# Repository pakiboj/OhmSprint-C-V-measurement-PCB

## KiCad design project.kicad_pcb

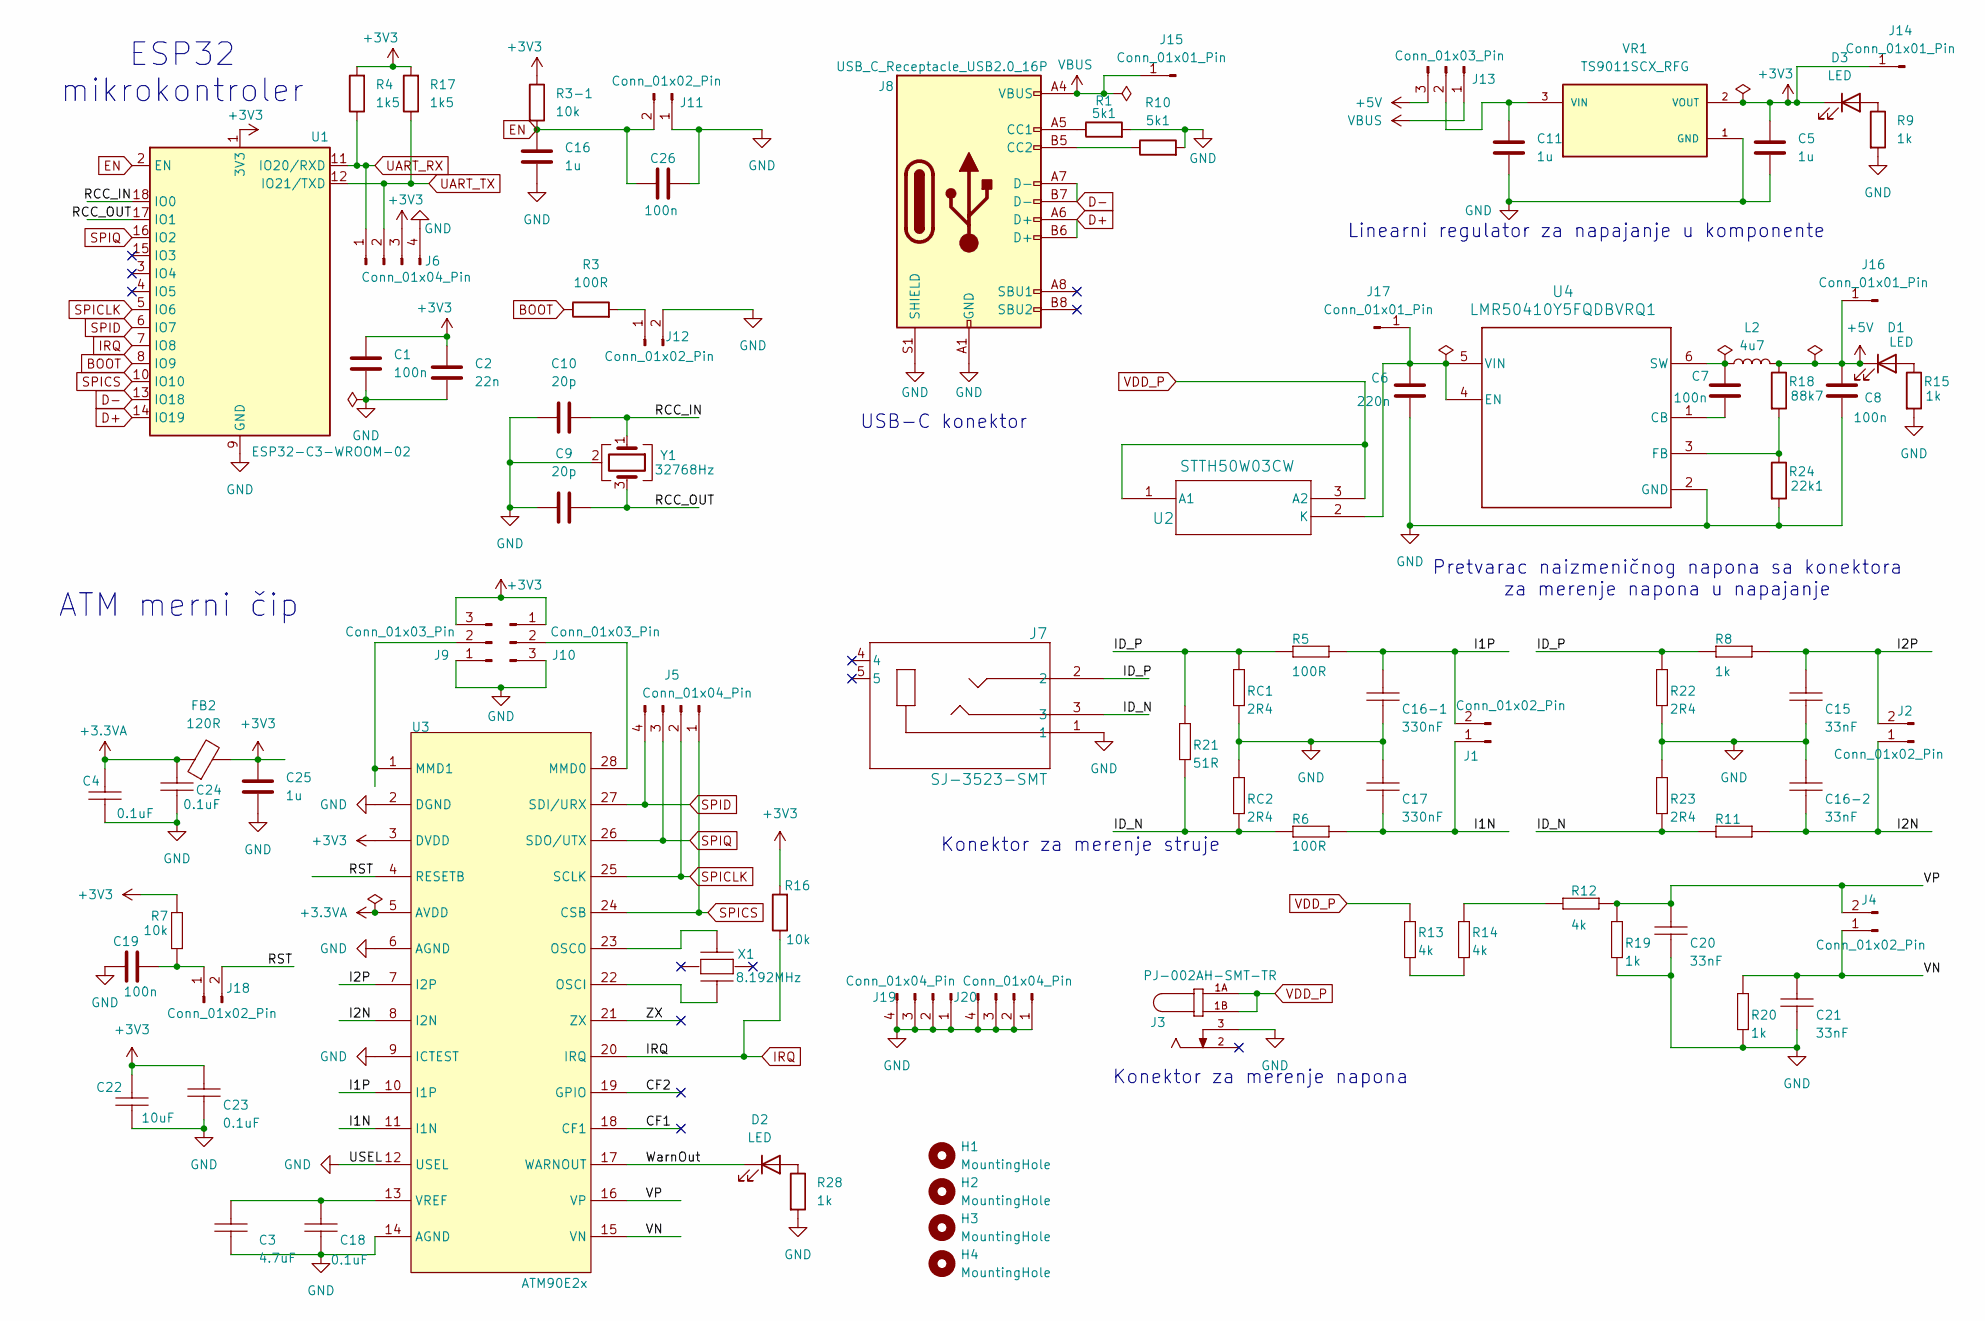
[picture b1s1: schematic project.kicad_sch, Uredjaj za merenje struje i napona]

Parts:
C1, C7, C8, C19, C26: 100n; C_0603_1608Metric; MPN 0603B104K250SD
C2: 22n; C_0603_1608Metric; MPN 0603B223K500SD
C3: 4.7uF; C_0805_2012Metric; MPN 0805B475K250CC
C4, C18: 0.1uF; C_0805_2012Metric; MPN 0805B104J500BD
C5, C11, C16, C25: 1u; C_0805_2012Metric; MPN 0805B105K250CC
C6: 220n; C_0805_2012Metric; MPN 0805B224K500CC
C9, C10: 20p; C_0603_1608Metric; MPN 0603N200J500SD
C15, C16-2, C20, C21: 33nF; C_0805_2012Metric; MPN 0805B333K500BD
C16-1, C17: 330nF; C_0603_1608Metric; MPN 0805B334K500CC
C22: 10uF; C_0805_2012Metric; MPN 0805B334K500CC
C23, C24: 0.1uF; C_0603_1608Metric; MPN 0603B104K250SD
D1, D2, D3: LED; D_1206_3216Metric; MPN XL-3216SURC
FB2: 120R; L_0805_2012Metric; MPN LI0805H121R-10
H1, H2, H3, H4: MountingHole; MountingHole_2mm
J1, J2, J4, J11, J12, J18: Conn_01x02_Pin; AMASS_XT30U-F_1x02_P5.0mm_Vertical; MPN PRPC002SAAN-RC
J3: PJ-002AH-SMT-TR; CUI_PJ-002AH-SMT-TR; MPN PJ-002AH-SMT-TR
J5, J6, J19, J20: Conn_01x04_Pin; FanPinHeader_1x04_P2.54mm_Vertical; MPN 68002-404HLF
J7: SJ-3523-SMT; SJ-3523-SMT_CUD; MPN SJ-3523-SMT-TR
J8: USB_C_Receptacle_USB2.0_16P; USB_C_Receptacle_GCT_USB4105-xx-A_16P_TopMnt_Horizontal; MPN UJ20-C-H-G-SMT-TR
J9, J10, J13: Conn_01x03_Pin; FanPinHeader_1x03_P2.54mm_Vertical; MPN 68001-203HLF
J14, J15, J16, J17: Conn_01x01_Pin; Hirose_DF63M-1P-3.96DSA_1x01_P3.96mm_Vertical; MPN 68000-101HLF
L2: 4u7; L_0805_2012Metric; MPN 0805LS-222XJRC
R1, R10: 5k1; R_0805_2012Metric; MPN CR0805-JW-512ELF
R3, R5, R6: 100R; R_0805_2012Metric; MPN CR0805-FX-1000ELF
R3-1, R7, R16: 10k; R_0805_2012Metric; MPN CR0805-FX-1002ELF
R4, R17: 1k5; R_0805_2012Metric; MPN CR0805-JW-152ELF
R8, R9, R11, R15, R19, R20, R28: 1k; R_0805_2012Metric; MPN CR0805-FX-1001ELF
R12, R13, R14: 4k; R_0805_2012Metric; MPN CR0805-FX-4021ELF
R18: 88k7; R_0805_2012Metric; MPN CR0805-FX-1001ELF
R21: 51R; R_0805_2012Metric; MPN CR0805-FX-51R0ELF
R22, R23: 2R4; R_0805_2012Metric; MPN CR0805-FX-2401ELF
R24: 22k1; R_0805_2012Metric; MPN CR0805-FX-1001ELF
RC1, RC2: 2R4; R_0805_2012Metric; MPN CR0805-FX-2401ELF
U1: ESP32-C3-WROOM-02; MPN ESP32-C3-WROOM-02-N4
U2: STTH50W03CW; TO-247_15P75X5P1_STM; MPN STTH50W03CW
U3: ATM90E2x; SSOP28_10P3X5P4_MCH; MPN ATM90E26-YU-R
U4: LMR50410Y5FQDBVRQ1; DBV0006A-IPC_C; MPN LMR50410Y5FQDBVRQ1
VR1: TS9011SCX_RFG; VREG_TS9011SCX_RFG; PARTREV I2402
X1: 8.192MHz; OSC_ECS-2520S25-250-FN-TR; MPN XTAL OSC XO 8.192MHZ CMOS SMD
Y1: 32768Hz; OSC_ECS-2520S25-250-FN-TR; MPN XTAL OSC XO 32.7680KHZ SMD

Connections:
+3.3VA: C4.2, C24.2, FB2.1, U3.5 (AVDD)
+3V3: C1.1, C2.1, C5.1, C22.1, C23.2, C25.1, D3.1 (K), FB2.2, J6.3, J9.3, J10.1, J14.1, R3-1.1, R4.2, R7.2, R16.2, R17.2, U1.1 (3V3), U3.3 (DVDD), VR1.2 (VOUT)
+5V: C8.1, D1.1 (K), J13.3, J16.1, L2.2, R18.1
/CF1: U3.18 (CF1)
/CF2: U3.19 (GPIO)
/I1N: C17.1, J1.1, R6.1, U3.11 (I1N)
/I1P: C16-1.2, J1.2, R5.1, U3.10 (I1P)
/I2N: C16-2.1, J2.1, R11.1, U3.8 (I2N)
/I2P: C15.2, J2.2, R8.1, U3.7 (I2P)
/ID_N: J7.3, R6.2, R11.2, R21.1, R23.1, RC2.1
/ID_P: J7.2, R5.2, R8.2, R21.2, R22.2, RC1.2
/RCC_IN: C10.2, U1.18 (IO0), Y1.1
/RCC_OUT: C9.2, U1.17 (IO1), Y1.3
/RST: J18.2, U3.4 (RESETB)
/VN: C21.2, J4.1, R20.2, U3.15 (VN)
/VP: C20.2, J4.2, R12.2, R19.2, U3.16 (VP)
/WarnOut: D2.1 (K), U3.17 (WARNOUT)
/ZX: U3.21 (ZX)
BOOT: R3.1, U1.8 (IO9)
D+: J8.A6 (D+), J8.B6 (D+), U1.14 (IO19)
D-: J8.A7 (D-), J8.B7 (D-), U1.13 (IO18)
EN: C16.1, C26.1, J11.2, R3-1.2, U1.2 (EN)
GND: C1.2, C2.2, C3.1, C4.1, C5.2, C6.2, C8.2, C9.1, C10.1, C11.2, C15.1, C16.2, C16-1.1, C16-2.2, C17.2, C18.1, C19.1, C20.1, C21.1, C22.2, C23.1, C24.1, C25.2, C26.2, J3.3, J6.4, J7.1, J8.A1 (GND), J8.A12 (GND), J8.B1 (GND), J8.B12 (GND), J8.S1 (SHIELD), J9.1, J10.3, J11.1, J12.2, J19.1, J19.2, J19.3, J19.4, J20.1, J20.2, J20.3, J20.4, R1.2, R9.2, R10.2, R15.2, R19.1, R20.1, R22.1, R23.2, R24.2, R28.2, RC1.1, RC2.2, U1.9 (GND), U1.19 (GND), U3.2 (DGND), U3.6 (AGND), U3.9 (ICTEST), U3.12 (USEL), U3.14 (AGND), U4.2 (GND), VR1.1 (GND), Y1.2 (G), Y1.4 (G)
IRQ: R16.1, U1.7 (IO8), U3.20 (IRQ)
unnamed: D1.2 (A), R15.1
unnamed: D2.2 (A), R28.1
unnamed: D3.2 (A), R9.1
unnamed: J8.A5 (CC1), R1.1
unnamed: J8.B5 (CC2), R10.1
unnamed: J9.2, U3.1 (MMD1)
unnamed: J10.2, U3.28 (MMD0)
unnamed: J12.1, R3.2
unnamed: C11.1, J13.2, VR1.3 (VIN)
unnamed: C6.1, J17.1, U2.2 (K), U4.4 (EN), U4.5 (VIN)
unnamed: C19.2, J18.1, R7.1
unnamed: R12.1, R14.1
unnamed: R13.2, R14.2
unnamed: U3.22 (OSCI), X1.2
unnamed: U3.23 (OSCO), X1.1
unnamed: C3.2, C18.2, U3.13 (VREF)
unnamed: C7.2, U4.1 (CB)
unnamed: R18.2, R24.1, U4.3 (FB)
unnamed: C7.1, L2.1, U4.6 (SW)
SPICLK: J5.2, U1.5 (IO6), U3.25 (SCLK)
SPICS: J5.1, U1.10 (IO10), U3.24 (CSB)
SPID: J5.4, U1.6 (IO7), U3.27 (SDI/URX)
SPIQ: J5.3, U1.16 (IO2), U3.26 (SDO/UTX)
UART_RX: J6.1, R4.1, U1.11 (IO20/RXD)
UART_TX: J6.2, R17.1, U1.12 (IO21/TXD)
VBUS: J8.A4 (VBUS), J8.A9 (VBUS), J8.B4 (VBUS), J8.B9 (VBUS), J13.1, J15.1
VDD_P: J3.1A, J3.1B, R13.1, U2.1 (A1), U2.3 (A2)

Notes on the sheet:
ATM merni čip
USB-C konektor
Konektor za merenje struje
ESP32 mikrokontroler
Konektor za merenje napona
Linearni regulator za napajanje u komponente
Pretvarac naizmeničnog napona sa konektora za merenje napona u napajanje

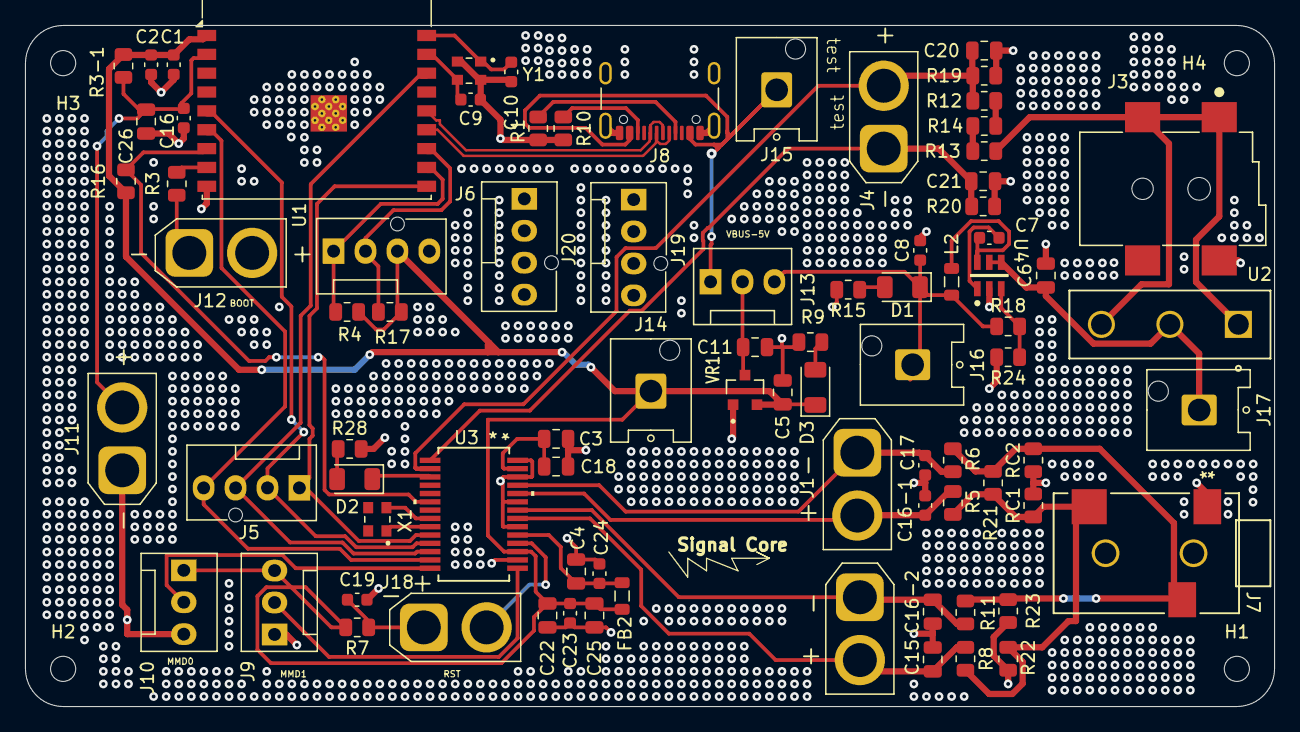
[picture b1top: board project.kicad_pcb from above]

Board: 2 copper layers, 99.4 x 54.2 mm, 88 parts (0 on the bottom side), 48 nets.

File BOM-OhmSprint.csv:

"Reference","Qty","Exclude from BOM","Exclude from Board","Datasheet","Footprint","Value","MANUFACTURER","MPN","link"
"C1,C7,C8,C19,C26","5","","","~","Capacitor_SMD:C_0603_1608Metric","100n","NextGen Components","0603B104K250SD","https://www.digikey.com/en/products/detail/nextgen-component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"
"C2","1","","","~","Capacitor_SMD:C_0603_1608Metric","22n","NextGen Components","0603B223K500SD","https://www.digikey.com/en/products/detail/nextgen-component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"
"C3","1","","","","Capacitor_SMD:C_0805_2012Metric","4.7uF","NextGen Components","0805B475K250CC","https://www.digikey.com/en/products/detail/nextgen-component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"
"C4,C18","2","","","","Capacitor_SMD:C_0805_2012Metric","0.1uF","NextGen Components","0805B104J500BD","https://www.digikey.com/en/products/detail/nextgen-component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"
"C5,C11,C16,C25","4","","","~","Capacitor_SMD:C_0805_2012Metric","1u","Aillen","0805B105K250CC","https://www.digikey.com/en/products/detail/nextgen-component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"
"C6","1","","","~","Capacitor_SMD:C_0805_2012Metric","220n","NextGen Components","0805B224K500CC","https://www.digikey.com/en/products/detail/nextgen-component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"
"C9,C10","2","","","~","Capacitor_SMD:C_0603_1608Metric","20p","NextGen Components","0603N200J500SD","https://www.digikey.com/en/products/detail/nextgen-component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"
"C15,C16-2,C20,C21","4","","","","Capacitor_SMD:C_0805_2012Metric","33nF","NextGen Components","0805B333K500BD","https://www.digikey.com/en/products/detail/nextgen-component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"
"C16-1,C17","2","","","","Capacitor_SMD:C_0603_1608Metric","330nF","NextGen Components","0805B334K500CC","https://www.digikey.com/en/products/detail/nextgen-component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"
"C22","1","","","","Capacitor_SMD:C_0805_2012Metric","10uF","NextGen Components","0805B334K500CC","https://www.digikey.com/en/products/detail/nextgen-component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"
"C23,C24","2","","","","Capacitor_SMD:C_0603_1608Metric","0.1uF","NextGen Components","0603B104K250SD","https://www.digikey.com/en/products/detail/nextgen-component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"
"D1,D2,D3","3","","","~","Diode_SMD:D_1206_3216Metric","LED","XINGLIGHT","XL-3216SURC","https://www.digikey.com/en/products/detail/xinglight/XL-3216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"
"FB2","1","","","~","Inductor_SMD:L_0805_2012Metric","120R","Laird-Signal Integrity Products","LI0805H121R-10","https://www.digikey.com/en/products/detail/laird-signal-inte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"
"H1,H2,H3,H4","4","Excluded from BOM","","~","MountingHole:MountingHole_2mm","MountingHole","","",""
"J1,J2,J4,J11,J12,J18","6","","","~","Connector_AMASS:AMASS_XT30U-F_1x02_P5.0mm_Vertical","Conn_01x02_Pin","Sullins Connector Solutions","PRPC002SAAN-RC","https://www.digikey.com/en/products/detail/sullins-connector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"
"J3","1","","","","OhmSprint:CUI_PJ-002AH-SMT-TR","PJ-002AH-SMT-TR","Same Sky (Formerly CUI Devices)","PJ-002AH-SMT-TR","https://www.digikey.com/en/products/detail/same-sky-formerly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"
"J5,J6,J19,J20","4","","","~","Connector:FanPinHeader_1x04_P2.54mm_Vertical","Conn_01x04_Pin","Amphenol ICC (FCI)","68002-404HLF","https://www.digikey.com/en/products/detail/amphenol-cs-fci/6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"
"J7","1","","","SJ-3523-SMT","OhmSprint:SJ-3523-SMT_CUD","SJ-3523-SMT","Same Sky (Formerly CUI Devices)","SJ-3523-SMT-TR","https://www.digikey.com/en/products/detail/same-sky-formerly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"
"J8","1","","","USB_C_Receptacle_USB2.0_16P","Connector_USB:USB_C_Receptacle_GCT_USB4105-xx-A_16P_TopMnt_Horizontal","USB_C_Receptacle_USB2.0_16P","Same Sky (Formerly CUI Devices)","UJ20-C-H-G-SMT-TR","https://www.digikey.com/en/products/detail/same-sky-formerly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"
"J9,J10,J13","3","","","~","Connector:FanPinHeader_1x03_P2.54mm_Vertical","Conn_01x03_Pin","Amphenol ICC (FCI)","68001-203HLF","https://www.digikey.com/en/products/detail/amphenol-cs-fci/6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"
"J14,J15,J16,J17","4","","","~","Connector_Hirose:Hirose_DF63M-1P-3.96DSA_1x01_P3.96mm_Vertical","Conn_01x01_Pin","Amphenol ICC (FCI)","68000-101HLF","https://www.digikey.com/en/products/detail/amphenol-cs-fci/6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"
"L2","1","","","~","Inductor_SMD:L_0805_2012Metric","4u7","Coilcraft","0805LS-222XJRC","https://www.digikey.com/en/products/detail/coilcraft/0805LS-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"
"R1,R10","2","","","~","Resistor_SMD:R_0805_2012Metric","5k1","Bourns Inc.","CR0805-JW-512ELF","https://www.digikey.com/en/products/detail/bourns-inc/CR0805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"
"R3,R5,R6","3","","","~","Resistor_SMD:R_0805_2012Metric","100R","Bourns Inc.","CR0805-FX-1000ELF","https://www.digikey.com/en/products/detail/bourns-inc/CR0805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"
"R3-1,R7,R16","3","","","~","Resistor_SMD:R_0805_2012Metric","10k","Bourns Inc.","CR0805-FX-1002ELF","https://www.digikey.com/en/products/detail/bourns-inc/CR0805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"
"R4,R17","2","","","~","Resistor_SMD:R_0805_2012Metric","1k5","Bourns Inc.","CR0805-JW-152ELF","https://www.digikey.com/en/products/detail/bourns-inc/CR0805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"
"R8,R9,R11,R15,R19,R20,R28","7","","","~","Resistor_SMD:R_0805_2012Metric","1k","Bourns Inc.","CR0805-FX-1001ELF","https://www.digikey.com/en/products/detail/bourns-inc/CR0805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"
"R12,R13,R14","3","","","","Resistor_SMD:R_0805_2012Metric","4k","Bourns Inc.","CR0805-FX-4021ELF","https://www.digikey.com/en/products/detail/bourns-inc/CR0805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"
"R18","1","","","~","Resistor_SMD:R_0805_2012Metric","88k7","Bourns Inc.","CR0805-FX-1001ELF","https://www.digikey.com/en/products/detail/bourns-inc/CR0805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"
"R21","1","","","","Resistor_SMD:R_0805_2012Metric","51R","Bourns Inc.","CR0805-FX-51R0ELF","https://www.digikey.com/en/products/detail/bourns-inc/CR0805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"
"R22,R23,RC1,RC2","4","","","","Resistor_SMD:R_0805_2012Metric","2R4","Bourns Inc.","CR0805-FX-2401ELF","https://www.digikey.com/en/products/detail/bourns-inc/CR0805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"
"R24","1","","","~","Resistor_SMD:R_0805_2012Metric","22k1","Bourns Inc.","CR0805-FX-1001ELF","https://www.digikey.com/en/products/detail/bourns-inc/CR0805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"
"U1","1","","","https://www.espressif.com/sites/default/files/documentation/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","RF_Module:ESP32-C3-WROOM-02","ESP32-C3-WROOM-02","Espressif Systems","ESP32-C3-WROOM-02-N4","https://www.digikey.com/en/products/detail/espressif-systems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"
"U2","1","","","https://www.st.com/resource/en/datasheet/stth50w03c.pdf","OhmSprint:TO-247_15P75X5P1_STM","STTH50W03CW","STMicroelectronics","STTH50W03CW","https://www.digikey.com/en/products/detail/stmicroelectronic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"
"U3","1","","","","OhmSprint:SSOP28_10P3X5P4_MCH","ATM90E2x","Microchip Technology","ATM90E26-YU-R","https://www.digikey.de/en/products/detail/microchip-technolo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"
"U4","1","","","https://www.ti.com/lit/gpn/lmr50410-q1","DBV0006A-IPC_A","LMR50410Y5FQDBVRQ1","Texas Instruments","LMR50410Y5FQDBVRQ1","https://www.digikey.com/en/products/detail/texas-instruments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"
"VR1","1","","","","OhmSprint:VREG_TS9011SCX_RFG","TS9011SCX_RFG","Taiwan Semiconductor","TS9011SCX RFG","https://www.digikey.com/en/products/detail/taiwan-semiconduc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"
"X1","1","","","","OhmSprint:OSC_ECS-2520S25-250-FN-TR","8.192MHz","ECS Inc.","XTAL OSC XO 8.192MHZ CMOS SMD","https://www.digikey.com/en/products/detail/ecs-inc/ECS-2520M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 "
"Y1","1","","","~","OhmSprint:OSC_ECS-2520S25-250-FN-TR","32768Hz","ECS Inc.","XTAL OSC XO 32.7680KHZ SMD","https://www.digikey.com/en/products/detail/ecs-inc/ECS-327MV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 "

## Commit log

2026-05-02 first first commit
